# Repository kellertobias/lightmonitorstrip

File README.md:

# Light Assistant

This tool is used in combination with a MagicQ light control desk to extend the amount of physical buttons on the desk.

It communicates via OSC to MagicQ and uses its HTTP API to update the available executors. It also interfaces with a gm1356 based SPL meter to display a little graph of how much the current DJ destroys your ears.

! This project is written by AI in large parts (as an experiment how far you can push it). That's why the code might not be super clean. The project however is fully functional and has been used to control lights for a few events.

## Project Layout:

```
light-assistant/
├── hardware/ # Hardware specific code and PCB schematics
├── src/
│ ├── app/ # NextJS frontend code
│ ├── components/ # React components
│ ├── contexts/ # React contexts
│ ├── hooks/ # React hooks
│ ├── mocks/ # Mock implementations of the interfacing systems to test against
│ ├── websocket-server/ # The Server to interface with the external systems
```

## Setup and running the project:

### Setup of Webserver & GUI:

- Run `npm install` to install the dependencies
- If you want to add the SPL meter, you need to install splread from here: https://github.com/pvachon/gm1356/tree/master
- Run `npm run dev` to start the development server(s)

You might want to run this on a raspberry PI and set it up so that it automatically starts when the pi starts and then opens the browser to the local webserver.

### MagicQ Setup

- Enable OSC (tx & rx) in the setup
- Enable the http server in the setup
- Create a grid of 10x10 executors on the MagicQ executor window (! only page 1 is supported)
- Each first line is the actual executor that will be controlled (contains the name of the executor)
- Each second line contains the color of the button in the grid, the type (Flash/ Toggle) and the color of the icon (e.g. `AAA,T,FF0` for a gray toggle button with a yellow icon)

### Setup of the Hardware:

- compile the arduino file (either the USB MIDI file or the USB Custom file)
- buy the PCB and solder it together
- upload the compiled arduino file to the microcontroller
- connect it via USB to this project

Alternatively the PCB also supports Hardware MIDI out (not tested yet) or DMX out (tested and works)

when you have flashed the USB Midi version and press the top left button while powering it up, you can select the
colors and brightness of the buttons' backlight. In the USB Custom version, the buttons' backlights are controlled by the server application and the DMX out of the board is disabled. In this mode it only interfaces with this project.

## AI Experiment

This project was an experiment to see how far you could push an AI to write an entire application. It started from an empty folder and the following prompt:

## Debugging

### Sending OSC Messages:

Install https://github.com/yoggy/sendosc

and then

```
sendosc 192.168.42.147 8000 /exec/1/12 f 0.6
```

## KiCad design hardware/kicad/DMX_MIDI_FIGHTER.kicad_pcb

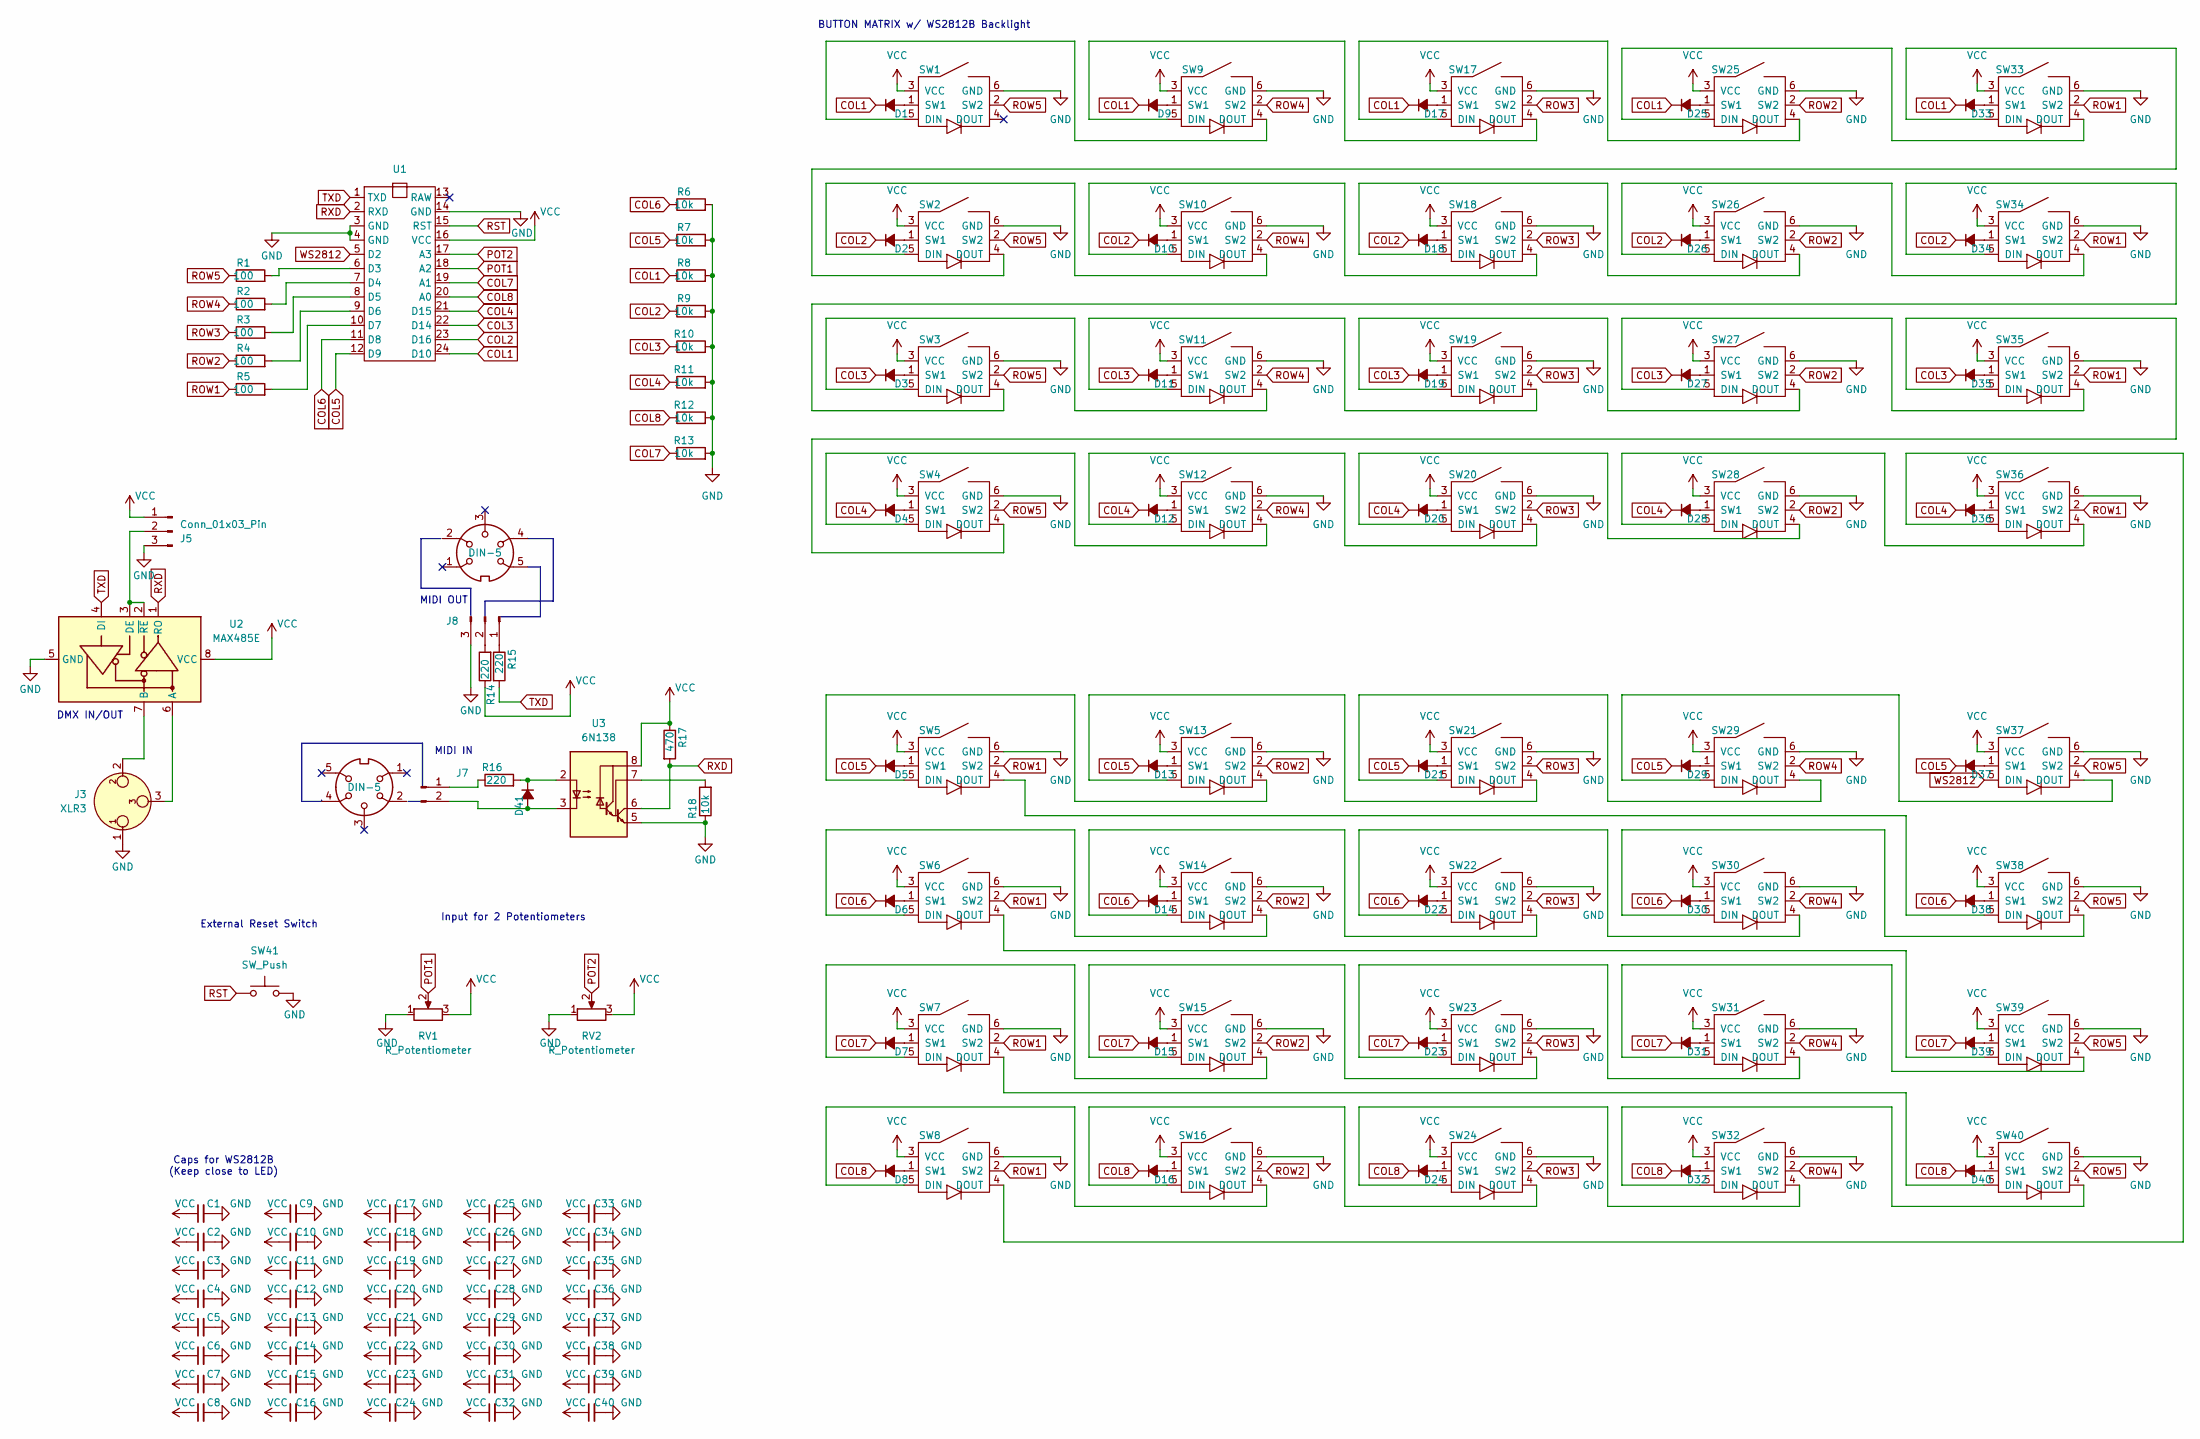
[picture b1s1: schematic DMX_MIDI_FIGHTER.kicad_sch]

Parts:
C1, C2, C3, C4, C5, C6, C7, C8, C9, C10, C11, C12, C13, C14, C15, C16, C17, C18, C19, C20, C21, C22, C23, C24, C25, C26, C27, C28, C29, C30, C31, C32, C33, C34, C35, C36, C37, C38, C39, C40: C_Small; C_0805_2012Metric; LCSC C28233
D1, D2, D3, D4, D5, D6, D7, D8, D9, D10, D11, D12, D13, D14, D15, D16, D17, D18, D19, D20, D21, D22, D23, D24, D25, D26, D27, D28, D29, D30, D31, D32, D33, D34, D35, D36, D37, D38, D39, D40, D41: D_Small_Filled; D_SOD-323; LCSC C2128
J3: XLR3; Jack_XLR_Neutrik_NC3FAH1-0_Horizontal
J4, J6: DIN-5; PinHeader_1x05_P2.54mm_Horizontal
J5: Conn_01x03_Pin; SW_CK_JS202011AQN_DPDT_Angled
J7: Conn_01x02_Pin; PinHeader_1x02_P2.54mm_Vertical
J8: Conn_01x03_Pin; PinHeader_1x03_P2.54mm_Vertical
R1, R2, R3, R4, R5: 100; R_0805_2012Metric_Pad1.20x1.40mm_HandSolder; LCSC C17408
R6, R7, R8, R9, R10, R11, R12, R13: 10k; R_0805_2012Metric_Pad1.20x1.40mm_HandSolder; LCSC C17414
R14, R15, R16: 220; R_Axial_DIN0411_L9.9mm_D3.6mm_P12.70mm_Horizontal
R17: 470; R_Axial_DIN0411_L9.9mm_D3.6mm_P12.70mm_Horizontal
R18: 10k; R_Axial_DIN0411_L9.9mm_D3.6mm_P12.70mm_Horizontal; LCSC C17414
RV1, RV2: R_Potentiometer; Potentiometer_Alps_RK09K_Single_Vertical
SW1, SW2, SW3, SW4, SW5, SW6, SW7, SW8, SW9, SW10, SW11, SW12, SW13, SW14, SW15, SW16, SW17, SW18, SW19, SW20, SW21, SW22, SW23, SW24, SW25, SW26, SW27, SW28, SW29, SW30, SW31, SW32, SW33, SW34, SW35, SW36, SW37, SW38, SW39, SW40: Switch_SW_WS2812B; Cherry_MX_SK6812_BS
SW41: SW_Push; SW_Tactile_SPST_Angled_PTS645Vx58-2LFS
U1: Arduino_PRO_MIcro_USB-C
U2: MAX485E; SOIC-8_3.9x4.9mm_P1.27mm
U3: 6N138; DIP-8_W7.62mm

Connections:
COL1: D1.1 (K), D9.1 (K), D17.1 (K), D25.1 (K), D33.1 (K), R8.1, U1.24 (D10)
COL2: D2.1 (K), D10.1 (K), D18.1 (K), D26.1 (K), D34.1 (K), R9.1, U1.23 (D16)
COL3: D3.1 (K), D11.1 (K), D19.1 (K), D27.1 (K), D35.1 (K), R10.1, U1.22 (D14)
COL4: D4.1 (K), D12.1 (K), D20.1 (K), D28.1 (K), D36.1 (K), R11.1, U1.21 (D15)
COL5: D5.1 (K), D13.1 (K), D21.1 (K), D29.1 (K), D37.1 (K), R7.1, U1.12 (D9)
COL6: D6.1 (K), D14.1 (K), D22.1 (K), D30.1 (K), D38.1 (K), R6.1, U1.11 (D8)
COL7: D7.1 (K), D15.1 (K), D23.1 (K), D31.1 (K), D39.1 (K), R13.1, U1.19 (A1)
COL8: D8.1 (K), D16.1 (K), D24.1 (K), D32.1 (K), D40.1 (K), R12.1, U1.20 (A0)
GND: C1.2, C2.2, C3.2, C4.2, C5.2, C6.2, C7.2, C8.2, C9.2, C10.2, C11.2, C12.2, C13.2, C14.2, C15.2, C16.2, C17.2, C18.2, C19.2, C20.2, C21.2, C22.2, C23.2, C24.2, C25.2, C26.2, C27.2, C28.2, C29.2, C30.2, C31.2, C32.2, C33.2, C34.2, C35.2, C36.2, C37.2, C38.2, C39.2, C40.2, J3.1, J5.3, J8.3, R6.2, R7.2, R8.2, R9.2, R10.2, R11.2, R12.2, R13.2, R18.1, RV1.1, RV2.1, SW1.6 (GND), SW2.6 (GND), SW3.6 (GND), SW4.6 (GND), SW5.6 (GND), SW6.6 (GND), SW7.6 (GND), SW8.6 (GND), SW9.6 (GND), SW10.6 (GND), SW11.6 (GND), SW12.6 (GND), SW13.6 (GND), SW14.6 (GND), SW15.6 (GND), SW16.6 (GND), SW17.6 (GND), SW18.6 (GND), SW19.6 (GND), SW20.6 (GND), SW21.6 (GND), SW22.6 (GND), SW23.6 (GND), SW24.6 (GND), SW25.6 (GND), SW26.6 (GND), SW27.6 (GND), SW28.6 (GND), SW29.6 (GND), SW30.6 (GND), SW31.6 (GND), SW32.6 (GND), SW33.6 (GND), SW34.6 (GND), SW35.6 (GND), SW36.6 (GND), SW37.6 (GND), SW38.6 (GND), SW39.6 (GND), SW40.6 (GND), SW41.2, U1.3 (GND), U1.4 (GND), U1.14 (GND), U2.5 (GND), U3.5 (GND)
unnamed: D1.2 (A), SW1.1 (SW1)
unnamed: D2.2 (A), SW2.1 (SW1)
unnamed: D3.2 (A), SW3.1 (SW1)
unnamed: D4.2 (A), SW4.1 (SW1)
unnamed: D5.2 (A), SW5.1 (SW1)
unnamed: D6.2 (A), SW6.1 (SW1)
unnamed: D7.2 (A), SW7.1 (SW1)
unnamed: D8.2 (A), SW8.1 (SW1)
unnamed: D9.2 (A), SW9.1 (SW1)
unnamed: D10.2 (A), SW10.1 (SW1)
unnamed: D11.2 (A), SW11.1 (SW1)
unnamed: D12.2 (A), SW12.1 (SW1)
unnamed: D13.2 (A), SW13.1 (SW1)
unnamed: D14.2 (A), SW14.1 (SW1)
unnamed: D15.2 (A), SW15.1 (SW1)
unnamed: D16.2 (A), SW16.1 (SW1)
unnamed: D17.2 (A), SW17.1 (SW1)
unnamed: D18.2 (A), SW18.1 (SW1)
unnamed: D19.2 (A), SW19.1 (SW1)
unnamed: D20.2 (A), SW20.1 (SW1)
unnamed: D21.2 (A), SW21.1 (SW1)
unnamed: D22.2 (A), SW22.1 (SW1)
unnamed: D23.2 (A), SW23.1 (SW1)
unnamed: D24.2 (A), SW24.1 (SW1)
unnamed: D25.2 (A), SW25.1 (SW1)
unnamed: D26.2 (A), SW26.1 (SW1)
unnamed: D27.2 (A), SW27.1 (SW1)
unnamed: D28.2 (A), SW28.1 (SW1)
unnamed: D29.2 (A), SW29.1 (SW1)
unnamed: D30.2 (A), SW30.1 (SW1)
unnamed: D31.2 (A), SW31.1 (SW1)
unnamed: D32.2 (A), SW32.1 (SW1)
unnamed: D33.2 (A), SW33.1 (SW1)
unnamed: D34.2 (A), SW34.1 (SW1)
unnamed: D35.2 (A), SW35.1 (SW1)
unnamed: D36.2 (A), SW36.1 (SW1)
unnamed: D37.2 (A), SW37.1 (SW1)
unnamed: D38.2 (A), SW38.1 (SW1)
unnamed: D39.2 (A), SW39.1 (SW1)
unnamed: D40.2 (A), SW40.1 (SW1)
unnamed: D41.2 (A), J7.2, U3.3 (C2)
unnamed: D41.1 (K), R16.2, U3.2 (C1)
unnamed: J5.2, U2.2 (~RE), U2.3 (DE)
unnamed: J7.1, R16.1
unnamed: J8.1, R15.1
unnamed: J8.2, R14.2
unnamed: SW1.5 (DIN), SW9.4 (DOUT)
unnamed: SW2.4 (DOUT), SW33.5 (DIN)
unnamed: SW3.4 (DOUT), SW34.5 (DIN)
unnamed: SW10.5 (DIN), SW18.4 (DOUT)
unnamed: SW2.5 (DIN), SW10.4 (DOUT)
unnamed: SW11.5 (DIN), SW19.4 (DOUT)
unnamed: SW3.5 (DIN), SW11.4 (DOUT)
unnamed: SW12.5 (DIN), SW20.4 (DOUT)
unnamed: SW4.5 (DIN), SW12.4 (DOUT)
unnamed: SW13.5 (DIN), SW21.4 (DOUT)
unnamed: SW5.5 (DIN), SW13.4 (DOUT)
unnamed: SW14.5 (DIN), SW22.4 (DOUT)
unnamed: SW6.5 (DIN), SW14.4 (DOUT)
unnamed: SW15.5 (DIN), SW23.4 (DOUT)
unnamed: SW7.5 (DIN), SW15.4 (DOUT)
unnamed: SW16.5 (DIN), SW24.4 (DOUT)
unnamed: SW8.5 (DIN), SW16.4 (DOUT)
unnamed: SW17.5 (DIN), SW25.4 (DOUT)
unnamed: SW9.5 (DIN), SW17.4 (DOUT)
unnamed: SW18.5 (DIN), SW26.4 (DOUT)
unnamed: SW19.5 (DIN), SW27.4 (DOUT)
unnamed: SW20.5 (DIN), SW28.4 (DOUT)
unnamed: SW21.5 (DIN), SW29.4 (DOUT)
unnamed: SW22.5 (DIN), SW30.4 (DOUT)
unnamed: SW23.5 (DIN), SW31.4 (DOUT)
unnamed: SW24.5 (DIN), SW32.4 (DOUT)
unnamed: SW25.5 (DIN), SW33.4 (DOUT)
unnamed: SW26.5 (DIN), SW34.4 (DOUT)
unnamed: SW27.5 (DIN), SW35.4 (DOUT)
unnamed: SW28.5 (DIN), SW36.4 (DOUT)
unnamed: SW29.5 (DIN), SW37.4 (DOUT)
unnamed: SW30.5 (DIN), SW38.4 (DOUT)
unnamed: SW31.5 (DIN), SW39.4 (DOUT)
unnamed: SW32.5 (DIN), SW40.4 (DOUT)
unnamed: SW4.4 (DOUT), SW35.5 (DIN)
unnamed: SW8.4 (DOUT), SW36.5 (DIN)
unnamed: SW5.4 (DOUT), SW38.5 (DIN)
unnamed: SW6.4 (DOUT), SW39.5 (DIN)
unnamed: SW7.4 (DOUT), SW40.5 (DIN)
unnamed: R1.2, U1.6 (D3)
unnamed: R2.2, U1.7 (D4)
unnamed: R3.2, U1.8 (D5)
unnamed: R4.2, U1.9 (D6)
unnamed: R5.2, U1.10 (D7)
unnamed: J3.3, U2.6 (A)
unnamed: J3.2, U2.7 (B)
unnamed: R18.2, U3.7 (VO1)
POT1: RV1.2, U1.18 (A2)
POT2: RV2.2, U1.17 (A3)
ROW1: R5.1, SW5.2 (SW2), SW6.2 (SW2), SW7.2 (SW2), SW8.2 (SW2), SW33.2 (SW2), SW34.2 (SW2), SW35.2 (SW2), SW36.2 (SW2)
ROW2: R4.1, SW13.2 (SW2), SW14.2 (SW2), SW15.2 (SW2), SW16.2 (SW2), SW25.2 (SW2), SW26.2 (SW2), SW27.2 (SW2), SW28.2 (SW2)
ROW3: R3.1, SW17.2 (SW2), SW18.2 (SW2), SW19.2 (SW2), SW20.2 (SW2), SW21.2 (SW2), SW22.2 (SW2), SW23.2 (SW2), SW24.2 (SW2)
ROW4: R2.1, SW9.2 (SW2), SW10.2 (SW2), SW11.2 (SW2), SW12.2 (SW2), SW29.2 (SW2), SW30.2 (SW2), SW31.2 (SW2), SW32.2 (SW2)
ROW5: R1.1, SW1.2 (SW2), SW2.2 (SW2), SW3.2 (SW2), SW4.2 (SW2), SW37.2 (SW2), SW38.2 (SW2), SW39.2 (SW2), SW40.2 (SW2)
RST: SW41.1, U1.15 (RST)
RXD: R17.2, U1.2 (RXD), U2.1 (RO), U3.6 (VO2)
TXD: R15.2, U1.1 (TXD), U2.4 (DI)
VCC: C1.1, C2.1, C3.1, C4.1, C5.1, C6.1, C7.1, C8.1, C9.1, C10.1, C11.1, C12.1, C13.1, C14.1, C15.1, C16.1, C17.1, C18.1, C19.1, C20.1, C21.1, C22.1, C23.1, C24.1, C25.1, C26.1, C27.1, C28.1, C29.1, C30.1, C31.1, C32.1, C33.1, C34.1, C35.1, C36.1, C37.1, C38.1, C39.1, C40.1, J5.1, R14.1, R17.1, RV1.3, RV2.3, SW1.3 (VCC), SW2.3 (VCC), SW3.3 (VCC), SW4.3 (VCC), SW5.3 (VCC), SW6.3 (VCC), SW7.3 (VCC), SW8.3 (VCC), SW9.3 (VCC), SW10.3 (VCC), SW11.3 (VCC), SW12.3 (VCC), SW13.3 (VCC), SW14.3 (VCC), SW15.3 (VCC), SW16.3 (VCC), SW17.3 (VCC), SW18.3 (VCC), SW19.3 (VCC), SW20.3 (VCC), SW21.3 (VCC), SW22.3 (VCC), SW23.3 (VCC), SW24.3 (VCC), SW25.3 (VCC), SW26.3 (VCC), SW27.3 (VCC), SW28.3 (VCC), SW29.3 (VCC), SW30.3 (VCC), SW31.3 (VCC), SW32.3 (VCC), SW33.3 (VCC), SW34.3 (VCC), SW35.3 (VCC), SW36.3 (VCC), SW37.3 (VCC), SW38.3 (VCC), SW39.3 (VCC), SW40.3 (VCC), U1.16 (VCC), U2.8 (VCC), U3.8 (VCC)
WS2812: SW37.5 (DIN), U1.5 (D2)

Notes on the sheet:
Input for 2 Potentiometers
External Reset Switch
BUTTON MATRIX w/ WS2812B Backlight
DMX IN/OUT
Caps for WS2812B (Keep close to LED)
MIDI IN
MIDI OUT

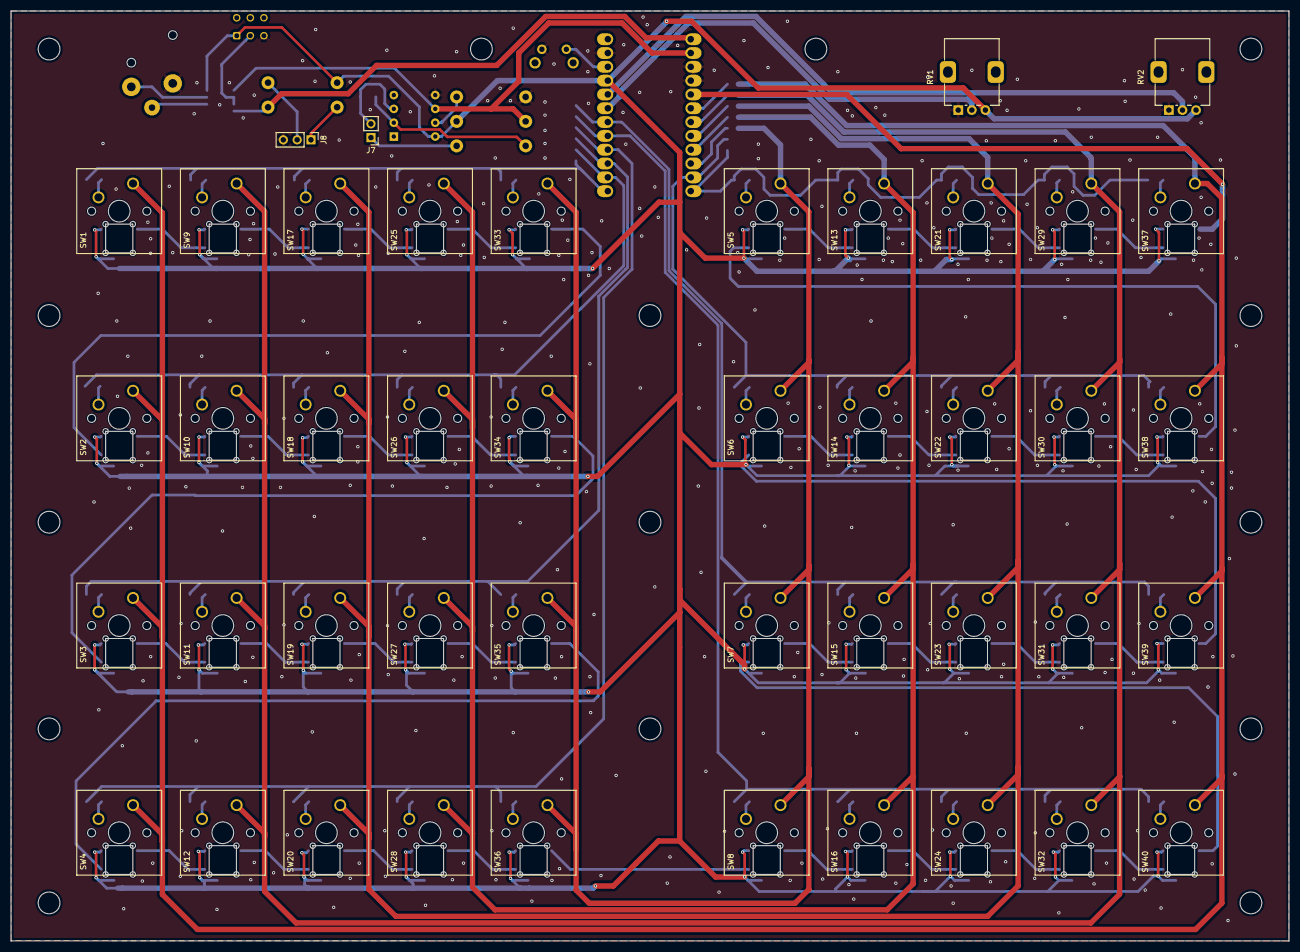
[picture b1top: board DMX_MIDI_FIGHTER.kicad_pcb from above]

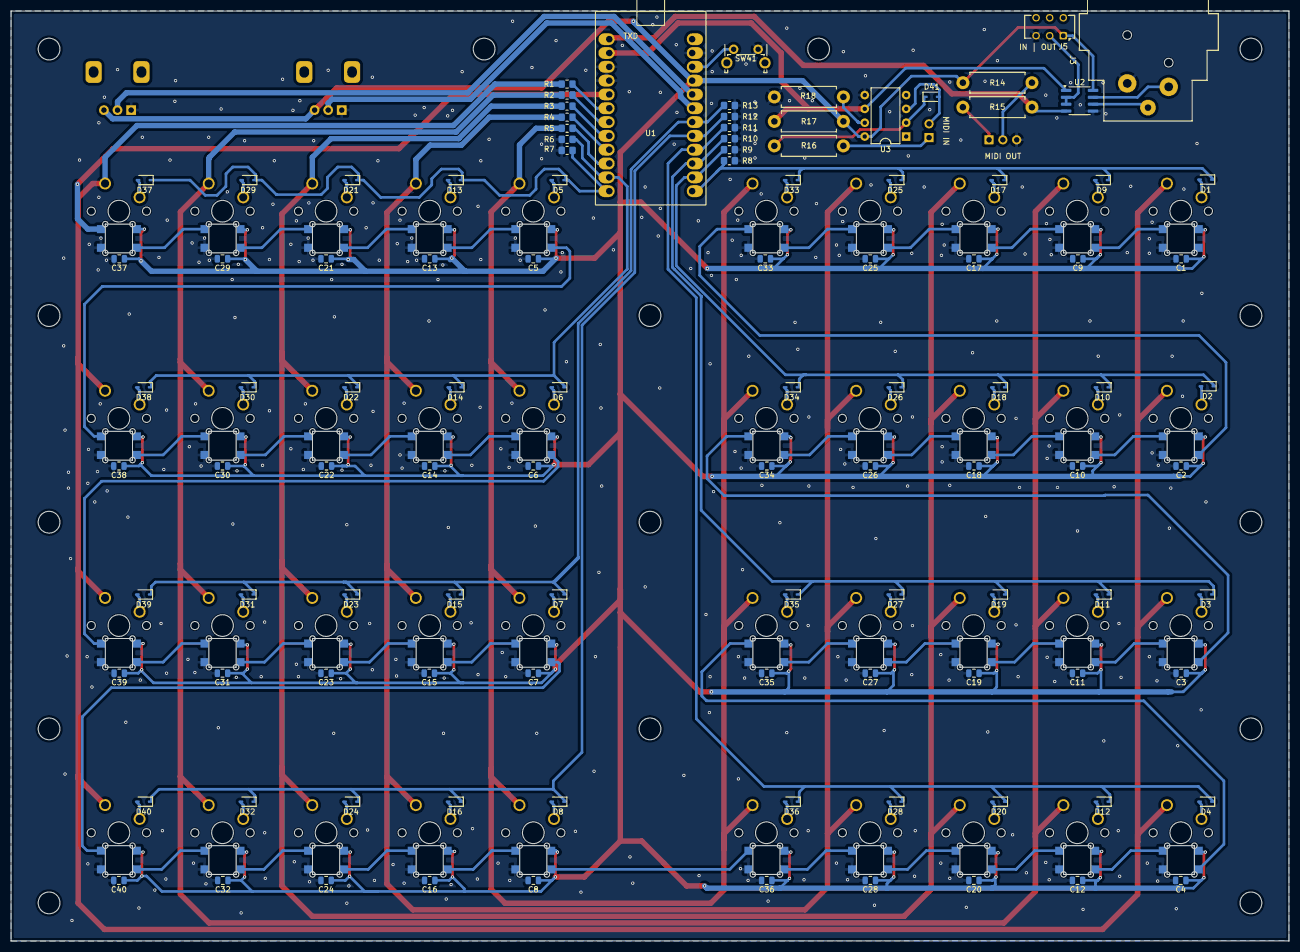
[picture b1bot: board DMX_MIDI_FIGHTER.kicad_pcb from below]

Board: 2 copper layers, 235.0 x 171.0 mm, 149 parts (105 on the bottom side), 114 nets.

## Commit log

2025-02-07 Initial commit from Create Next App
2025-02-07 websockets
2025-02-07 fix: tailwind working
2025-02-08 feat: spl meter
2025-02-08 kill others
2025-02-08 start correct SPL meter
2025-02-08 don't crash
2025-02-08 handle missing error
2025-02-08 hide cursor
2025-02-08 faster shutdown
2025-02-08 slower graph
2025-02-08 slow graph down
2025-02-08 improve UI
2025-02-09 add reload from magicq
2025-02-09 fix osc receive
2025-02-09 force float
2025-02-15 Add hardware design files and firmware for MIDI/DMX controller
    - Added KiCad PCB design files for DMX_MIDI_FIGHTER project
    - Included firmware for USB MIDI controller with button matrix and LED control
    - Added hardware schematics and enclosure design files
    - Updated README with project details and hardware setup instructions
    - Removed unused public SVG assets
    - Added initial unit tests for websocket server helpers
2025-02-15 Fix import path for websocket server helpers test
2025-02-15 Add project screenshot to README
2025-02-16 Add button controller firmware for Light Assistant project
    - Implemented 40-button matrix controller firmware
    - Added RGB LED feedback with configurable brightness
    - Supported serial communication protocol for button and potentiometer states
    - Included matrix scanning, debouncing, and LED control logic
